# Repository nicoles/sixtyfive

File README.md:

# sixtyfive
 
A 65% keyboard. Using https://github.com/AcheronProject/Tsuki as a guide, wish me luck?

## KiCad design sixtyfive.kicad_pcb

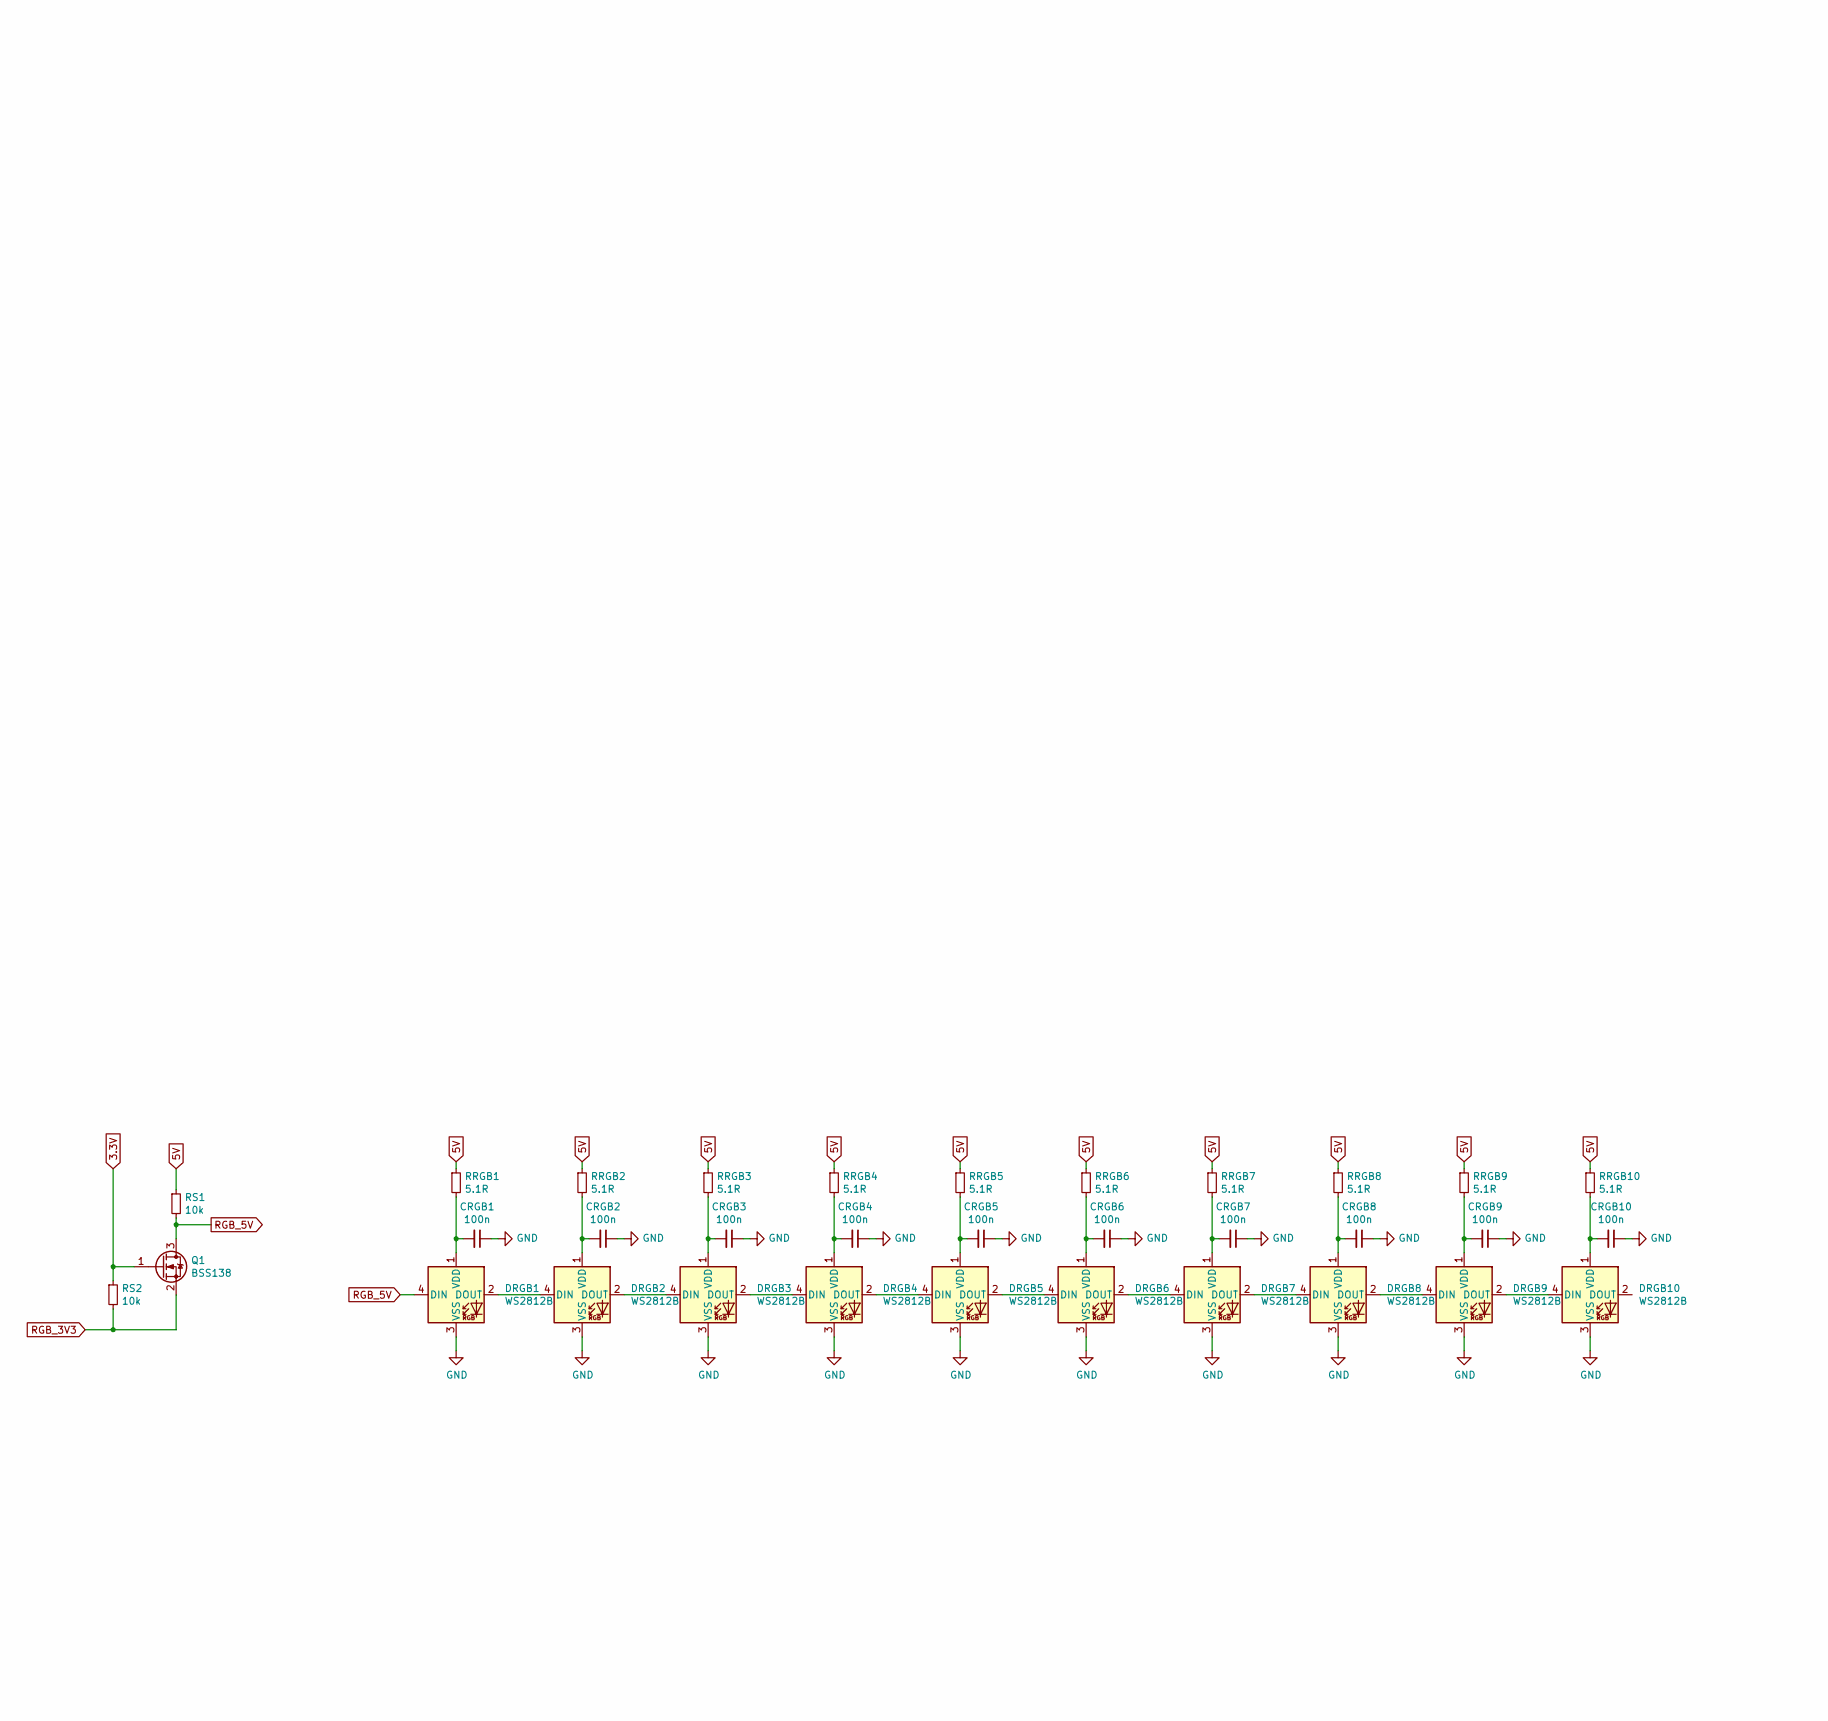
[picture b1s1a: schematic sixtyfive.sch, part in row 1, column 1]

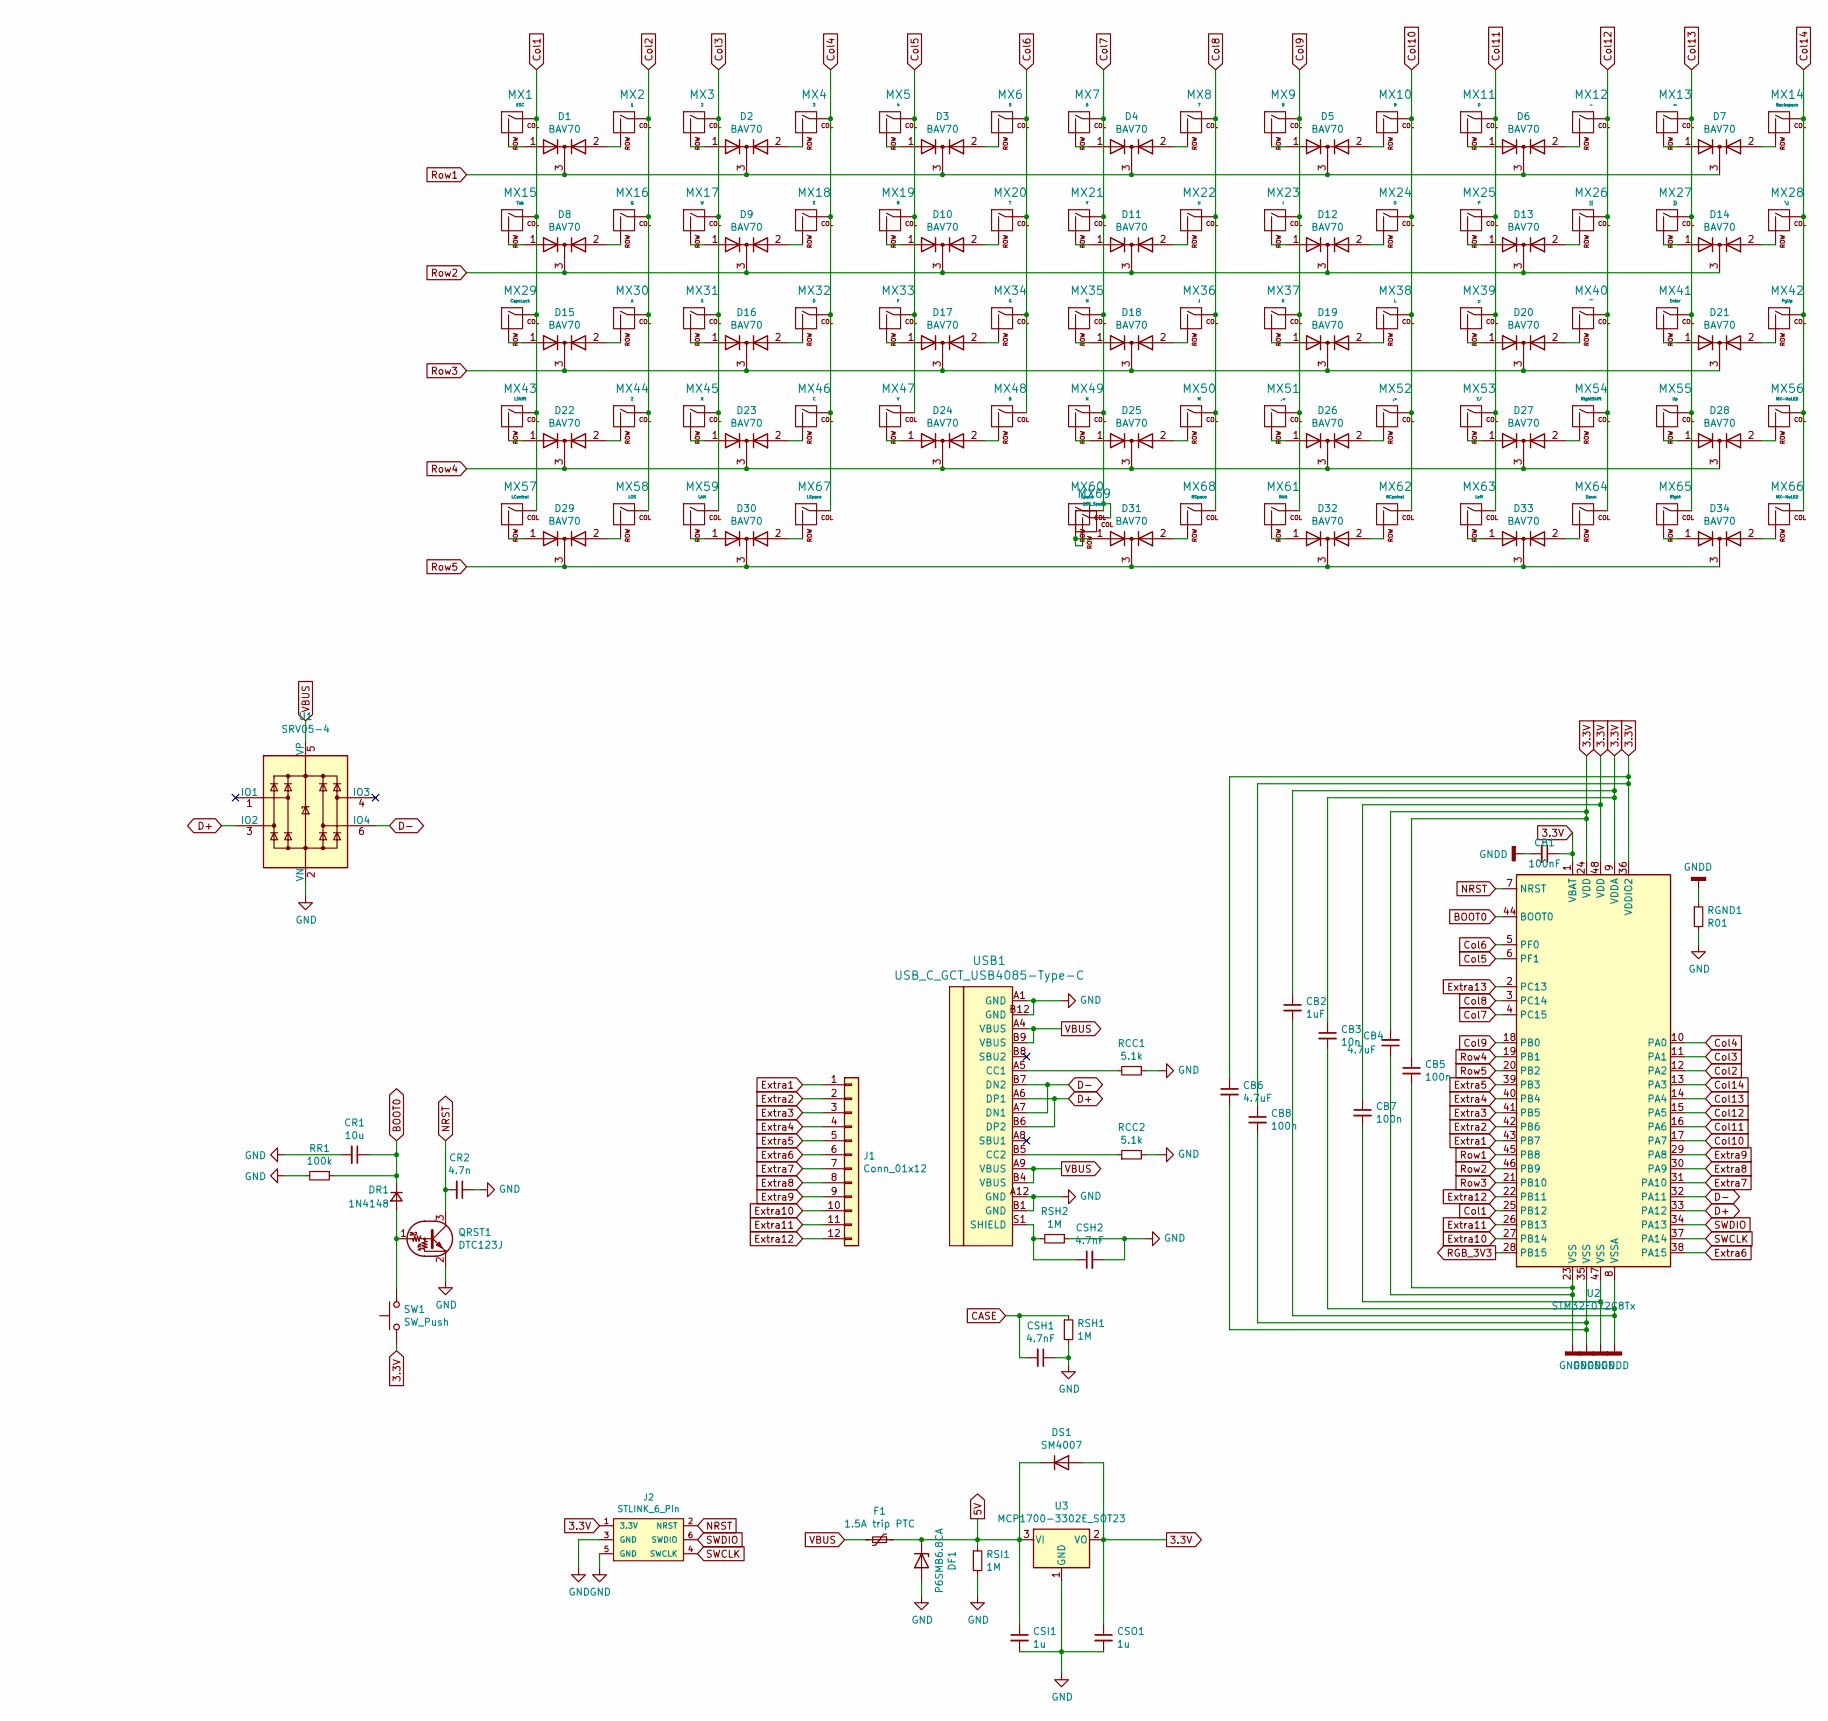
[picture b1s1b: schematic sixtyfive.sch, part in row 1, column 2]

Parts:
CB1: 100nF; C_0402_1005Metric; JLCCode C1525
CB2: 1uF; C_0402_1005Metric; JLCCode C52923
CB3: 10n; C_0402_1005Metric; JLCCode C15195
CB4, CB6: 4.7uF; C_0402_1005Metric; JLCCode C23733
CB5, CB7, CB8: 100n; C_0402_1005Metric; JLCCode C1525
CR1: 10u; C_0805_2012Metric; JLCCode C15850
CR2: 4.7n; C_0805_2012Metric; JLCCode C1744
CRGB1, CRGB2, CRGB3, CRGB4, CRGB5, CRGB6, CRGB7, CRGB8, CRGB9, CRGB10: 100n; C_0805_2012Metric
CSH1, CSH2: 4.7nF; C_0805_2012Metric; JLCCode C1744
CSI1: 1u; C_0805_2012Metric; JLCCode C28323
CSO1: 1u; C_0805_2012Metric; JLCCode C28323
D1, D2, D3, D4, D5, D6, D7, D8, D9, D10, D11, D12, D13, D14, D15, D16, D17, D18, D19, D20, D21, D22, D23, D24, D25, D26, D27, D28, D29, D30, D31, D32, D33, D34: BAV70; SOT-23; JLCCode C68978
DF1: P6SMB6.8CA; D_SMB; JLCCode C78395
DR1: 1N4148; D_SOD-123; JLCCode C81598
DRGB1, DRGB2, DRGB3, DRGB4, DRGB5, DRGB6, DRGB7, DRGB8, DRGB9, DRGB10: WS2812B; LED_WS2812B_PLCC4_5.0x5.0mm_P3.2mm; JLCCode C114586
DS1: SM4007; D_SOD-123F; JLCCode C64898
F1: 1.5A trip PTC; Fuse_1812_4532Metric; JLCCode C84140
J1: Conn_01x12; PinHeader_1x12_P2.54mm_Vertical
J2: STLINK_6_Pin; 2X3_LOCK
MX1: ESC; MXOnly-1U-Hotswap
MX2: 1; MXOnly-1U-Hotswap
MX3: 2; MXOnly-1U-Hotswap
MX4: 3; MXOnly-1U-Hotswap
MX5: 4; MXOnly-1U-Hotswap
MX6: 5; MXOnly-1U-Hotswap
MX7: 6; MXOnly-1U-Hotswap
MX8: 7; MXOnly-1U-Hotswap
MX9: 8; MXOnly-1U-Hotswap
MX10: 9; MXOnly-1U-Hotswap
MX11: 0; MXOnly-1U-Hotswap
MX12: -; MXOnly-1U-Hotswap
MX13: =; MXOnly-1U-Hotswap
MX14: Backspace; MXOnly-2U-Hotswap
MX15: Tab; MXOnly-1.5U-Hotswap
MX16: Q; MXOnly-1U-Hotswap
MX17: W; MXOnly-1U-Hotswap
MX18: E; MXOnly-1U-Hotswap
MX19: R; MXOnly-1U-Hotswap
MX20: T; MXOnly-1U-Hotswap
MX21: Y; MXOnly-1U-Hotswap
MX22: U; MXOnly-1U-Hotswap
MX23: I; MXOnly-1U-Hotswap
MX24: O; MXOnly-1U-Hotswap
MX25: P; MXOnly-1U-Hotswap
MX26: [{; MXOnly-1U-Hotswap
MX27: ]}; MXOnly-1U-Hotswap
MX28: \\|; MXOnly-1.5U-Hotswap
MX29: CapsLock; MXOnly-1.75U-Hotswap
MX30: A; MXOnly-1U-Hotswap
MX31: S; MXOnly-1U-Hotswap
MX32: D; MXOnly-1U-Hotswap
MX33: F; MXOnly-1U-Hotswap
MX34: G; MXOnly-1U-Hotswap
MX35: H; MXOnly-1U-Hotswap
MX36: J; MXOnly-1U-Hotswap
MX37: K; MXOnly-1U-Hotswap
MX38: L; MXOnly-1U-Hotswap
MX39: :;; MXOnly-1U-Hotswap
MX40: \"'; MXOnly-1U-Hotswap
MX41: Enter; MXOnly-2.25U-Hotswap
MX42: PgUp; MXOnly-1U-Hotswap
MX43: LShift; MXOnly-2.25U-Hotswap
MX44: Z; MXOnly-1U-Hotswap
MX45: X; MXOnly-1U-Hotswap
MX46: C; MXOnly-1U-Hotswap
MX47: V; MXOnly-1U-Hotswap
MX48: B; MXOnly-1U-Hotswap
MX49: N; MXOnly-1U-Hotswap
MX50: M; MXOnly-1U-Hotswap
MX51: ,<; MXOnly-1U-Hotswap
MX52: .>; MXOnly-1U-Hotswap
MX53: ?/; MXOnly-1U-Hotswap
MX54: RightShift; MXOnly-1.75U-Hotswap
MX55: Up; MXOnly-1U-Hotswap
MX56, MX66: MX-NoLED; MXOnly-1U-Hotswap
MX57: LControl; MXOnly-1.25U-Hotswap
MX58: LOS; MXOnly-1.25U-Hotswap
MX59: LAlt; MXOnly-1.25U-Hotswap
MX60: Space; MXOnly-6.25U-Hotswap-ReversedStabilizers
MX61: RAlt; MXOnly-1.25U-Hotswap
MX62: RControl; MXOnly-1.25U-Hotswap
MX63: Left; MXOnly-1U-Hotswap
MX64: Down; MXOnly-1U-Hotswap
MX65: Right; MXOnly-1U-Hotswap
MX67: LSpace; MXOnly-2.75U-Hotswap
MX68: RSpace; MXOnly-2.25U-Hotswap
MX69: 125_Space; MXOnly-1.25U-Hotswap
Q1: BSS138; SOT-23; JLCCode C193019
QRST1: DTC123J; SOT-23; JLCCode C111724
RCC1, RCC2: 5.1k; R_0805_2012Metric; JLCCode C27834
RGND1: R01; R_1206_3216Metric; JLCCode C127703
RR1: 100k; R_1206_3216Metric; JLCCode C17900
RRGB1, RRGB2, RRGB3, RRGB4, RRGB5, RRGB6, RRGB7, RRGB8, RRGB9, RRGB10: 5.1R; R_0805_2012Metric; JLCCode C17724
RS1, RS2: 10k; R_1206_3216Metric; JLCCode C17902
RSH1, RSH2: 1M; R_0805_2012Metric; JLCCode C17514
RSI1: 1M; R_0805_2012Metric; JLCCode C17514
SW1: SW_Push; smdPushBtn; JLCCode C318884
U1: SRV05-4; SOT-23-6; JLCCode C85364
U2: STM32F072C8Tx; LQFP-48_7x7mm_P0.5mm; JLCCode C80488
U3: MCP1700-3302E_SOT23; SOT-23; JLCCode C39051
USB1: USB_C_GCT_USB4085-Type-C; USB_C_Receptacle_GCT_USB4085

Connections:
5V: CSI1.1, DF1.1 (K), DS1.1 (K), F1.1, RRGB1.1, RRGB2.1, RRGB3.1, RRGB4.1, RRGB5.1, RRGB6.1, RRGB7.1, RRGB8.1, RRGB9.1, RRGB10.1, RS1.1, RSI1.1, U3.3 (VI)
+3V3: CB1.1, CB2.1, CB3.1, CB4.2, CB5.1, CB6.1, CB7.1, CB8.1, CSO1.1, DS1.2 (A), J2.1 (3.3V), Q1.1 (G), RS2.1, SW1.1, U2.1 (VBAT), U2.9 (VDDA), U2.24 (VDD), U2.36 (VDDIO2), U2.48 (VDD), U3.2 (VO)
BOOT0: CR1.1, DR1.1 (K), RR1.1, U2.44 (BOOT0)
CASE: CSH1.2, RSH1.1
Col1: MX1.1 (COL), MX15.1 (COL), MX29.1 (COL), MX43.1 (COL), MX57.1 (COL), U2.25 (PB12)
Col2: MX2.1 (COL), MX16.1 (COL), MX30.1 (COL), MX44.1 (COL), MX58.1 (COL), U2.12 (PA2)
Col3: MX3.1 (COL), MX17.1 (COL), MX31.1 (COL), MX45.1 (COL), MX59.1 (COL), U2.11 (PA1)
Col4: MX4.1 (COL), MX18.1 (COL), MX32.1 (COL), MX46.1 (COL), MX67.1 (COL), U2.10 (PA0)
Col5: MX5.1 (COL), MX19.1 (COL), MX33.1 (COL), MX47.1 (COL), U2.6 (PF1)
Col6: MX6.1 (COL), MX20.1 (COL), MX34.1 (COL), MX48.1 (COL), U2.5 (PF0)
Col7: MX7.1 (COL), MX21.1 (COL), MX35.1 (COL), MX49.1 (COL), MX60.1 (COL), MX69.1 (COL), U2.4 (PC15)
Col8: MX8.1 (COL), MX22.1 (COL), MX36.1 (COL), MX50.1 (COL), MX68.1 (COL), U2.3 (PC14)
Col9: MX9.1 (COL), MX23.1 (COL), MX37.1 (COL), MX51.1 (COL), MX61.1 (COL), U2.18 (PB0)
Col10: MX10.1 (COL), MX24.1 (COL), MX38.1 (COL), MX52.1 (COL), MX62.1 (COL), U2.17 (PA7)
Col11: MX11.1 (COL), MX25.1 (COL), MX39.1 (COL), MX53.1 (COL), MX63.1 (COL), U2.16 (PA6)
Col12: MX12.1 (COL), MX26.1 (COL), MX40.1 (COL), MX54.1 (COL), MX64.1 (COL), U2.15 (PA5)
Col13: MX13.1 (COL), MX27.1 (COL), MX41.1 (COL), MX55.1 (COL), MX65.1 (COL), U2.14 (PA4)
Col14: MX14.1 (COL), MX28.1 (COL), MX42.1 (COL), MX56.1 (COL), MX66.1 (COL), U2.13 (PA3)
D+: U1.3 (IO2), U2.33 (PA12), USB1.A6 (DP1), USB1.B6 (DP2)
D-: U1.6 (IO4), U2.32 (PA11), USB1.A7 (DN1), USB1.B7 (DN2)
Extra1: J1.1, U2.43 (PB7)
Extra2: J1.2, U2.42 (PB6)
Extra3: J1.3, U2.41 (PB5)
Extra4: J1.4, U2.40 (PB4)
Extra5: J1.5, U2.39 (PB3)
Extra6: J1.6, U2.38 (PA15)
Extra7: J1.7, U2.31 (PA10)
Extra8: J1.8, U2.30 (PA9)
Extra9: J1.9, U2.29 (PA8)
Extra10: J1.10, U2.27 (PB14)
Extra11: J1.11, U2.26 (PB13)
Extra12: J1.12, U2.22 (PB11)
GND: CR1.2, CR2.1, CRGB1.1, CRGB2.1, CRGB3.1, CRGB4.1, CRGB5.1, CRGB6.1, CRGB7.1, CRGB8.1, CRGB9.1, CRGB10.1, CSH1.1, CSH2.2, CSI1.2, CSO1.2, DF1.2 (A), DRGB1.3 (VSS), DRGB2.3 (VSS), DRGB3.3 (VSS), DRGB4.3 (VSS), DRGB5.3 (VSS), DRGB6.3 (VSS), DRGB7.3 (VSS), DRGB8.3 (VSS), DRGB9.3 (VSS), DRGB10.3 (VSS), J2.3 (GND), J2.5 (GND), QRST1.2 (E), RCC1.1, RCC2.2, RGND1.2, RR1.2, RSH1.2, RSH2.1, RSI1.2, U1.2 (VN), U3.1 (GND), USB1.A1 (GND), USB1.A12 (GND), USB1.B1 (GND), USB1.B12 (GND)
GNDD: CB1.2, CB2.2, CB3.2, CB4.1, CB5.2, CB6.2, CB7.2, CB8.2, RGND1.1, U2.8 (VSSA), U2.23 (VSS), U2.35 (VSS), U2.47 (VSS)
NRST: CR2.2, J2.2 (NRST), QRST1.3 (C), U2.7 (NRST)
unnamed: CRGB1.2, DRGB1.1 (VDD), RRGB1.2
unnamed: CRGB2.2, DRGB2.1 (VDD), RRGB2.2
unnamed: CRGB3.2, DRGB3.1 (VDD), RRGB3.2
unnamed: CRGB4.2, DRGB4.1 (VDD), RRGB4.2
unnamed: CRGB5.2, DRGB5.1 (VDD), RRGB5.2
unnamed: CRGB6.2, DRGB6.1 (VDD), RRGB6.2
unnamed: CRGB7.2, DRGB7.1 (VDD), RRGB7.2
unnamed: CRGB8.2, DRGB8.1 (VDD), RRGB8.2
unnamed: CRGB9.2, DRGB9.1 (VDD), RRGB9.2
unnamed: CRGB10.2, DRGB10.1 (VDD), RRGB10.2
unnamed: CSH2.1, RSH2.2, USB1.S1 (SHIELD)
unnamed: D1.1 (A), MX1.2 (ROW)
unnamed: D1.2 (A), MX2.2 (ROW)
unnamed: D2.1 (A), MX3.2 (ROW)
unnamed: D2.2 (A), MX4.2 (ROW)
unnamed: D3.1 (A), MX5.2 (ROW)
unnamed: D3.2 (A), MX6.2 (ROW)
unnamed: D4.1 (A), MX7.2 (ROW)
unnamed: D4.2 (A), MX8.2 (ROW)
unnamed: D5.1 (A), MX9.2 (ROW)
unnamed: D5.2 (A), MX10.2 (ROW)
unnamed: D6.1 (A), MX11.2 (ROW)
unnamed: D6.2 (A), MX12.2 (ROW)
unnamed: D7.1 (A), MX13.2 (ROW)
unnamed: D7.2 (A), MX14.2 (ROW)
unnamed: D8.1 (A), MX15.2 (ROW)
unnamed: D8.2 (A), MX16.2 (ROW)
unnamed: D9.1 (A), MX17.2 (ROW)
unnamed: D9.2 (A), MX18.2 (ROW)
unnamed: D10.1 (A), MX19.2 (ROW)
unnamed: D10.2 (A), MX20.2 (ROW)
unnamed: D11.1 (A), MX21.2 (ROW)
unnamed: D11.2 (A), MX22.2 (ROW)
unnamed: D12.1 (A), MX23.2 (ROW)
unnamed: D12.2 (A), MX24.2 (ROW)
unnamed: D13.1 (A), MX25.2 (ROW)
unnamed: D13.2 (A), MX26.2 (ROW)
unnamed: D14.1 (A), MX27.2 (ROW)
unnamed: D14.2 (A), MX28.2 (ROW)
unnamed: D15.1 (A), MX29.2 (ROW)
unnamed: D15.2 (A), MX30.2 (ROW)
unnamed: D16.1 (A), MX31.2 (ROW)
unnamed: D16.2 (A), MX32.2 (ROW)
unnamed: D17.1 (A), MX33.2 (ROW)
unnamed: D17.2 (A), MX34.2 (ROW)
unnamed: D18.1 (A), MX35.2 (ROW)
unnamed: D18.2 (A), MX36.2 (ROW)
unnamed: D19.1 (A), MX37.2 (ROW)
unnamed: D19.2 (A), MX38.2 (ROW)
unnamed: D20.1 (A), MX39.2 (ROW)
unnamed: D20.2 (A), MX40.2 (ROW)
unnamed: D21.1 (A), MX41.2 (ROW)
unnamed: D21.2 (A), MX42.2 (ROW)
unnamed: D22.1 (A), MX43.2 (ROW)
unnamed: D22.2 (A), MX44.2 (ROW)
unnamed: D23.1 (A), MX45.2 (ROW)
unnamed: D23.2 (A), MX46.2 (ROW)
unnamed: D24.1 (A), MX47.2 (ROW)
unnamed: D24.2 (A), MX48.2 (ROW)
unnamed: D25.1 (A), MX49.2 (ROW)
unnamed: D25.2 (A), MX50.2 (ROW)
unnamed: D26.1 (A), MX51.2 (ROW)
unnamed: D26.2 (A), MX52.2 (ROW)
unnamed: D27.1 (A), MX53.2 (ROW)
unnamed: D27.2 (A), MX54.2 (ROW)
unnamed: D28.1 (A), MX55.2 (ROW)
unnamed: D28.2 (A), MX56.2 (ROW)
unnamed: D29.1 (A), MX57.2 (ROW)
unnamed: D29.2 (A), MX58.2 (ROW)
unnamed: D30.1 (A), MX59.2 (ROW)
unnamed: D30.2 (A), MX67.2 (ROW)
unnamed: D31.1 (A), MX60.2 (ROW), MX69.2 (ROW)
unnamed: D31.2 (A), MX68.2 (ROW)
unnamed: D32.1 (A), MX61.2 (ROW)
unnamed: D32.2 (A), MX62.2 (ROW)
unnamed: D33.1 (A), MX63.2 (ROW)
unnamed: D33.2 (A), MX64.2 (ROW)
unnamed: D34.1 (A), MX65.2 (ROW)
unnamed: D34.2 (A), MX66.2 (ROW)
unnamed: DR1.2 (A), QRST1.1 (B), SW1.2
unnamed: DRGB1.2 (DOUT), DRGB2.4 (DIN)
unnamed: DRGB2.2 (DOUT), DRGB3.4 (DIN)
unnamed: DRGB3.2 (DOUT), DRGB4.4 (DIN)
unnamed: DRGB4.2 (DOUT), DRGB5.4 (DIN)
unnamed: DRGB5.2 (DOUT), DRGB6.4 (DIN)
unnamed: DRGB6.2 (DOUT), DRGB7.4 (DIN)
unnamed: DRGB7.2 (DOUT), DRGB8.4 (DIN)
unnamed: DRGB8.2 (DOUT), DRGB9.4 (DIN)
unnamed: DRGB9.2 (DOUT), DRGB10.4 (DIN)
unnamed: RCC1.2, USB1.A5 (CC1)
unnamed: RCC2.1, USB1.B5 (CC2)
RGB_3V3: Q1.2 (S), RS2.2, U2.28 (PB15)
RGB_5V: DRGB1.4 (DIN), Q1.3 (D), RS1.2
Row1: D1.3 (K), D2.3 (K), D3.3 (K), D4.3 (K), D5.3 (K), D6.3 (K), D7.3 (K), U2.45 (PB8)
Row2: D8.3 (K), D9.3 (K), D10.3 (K), D11.3 (K), D12.3 (K), D13.3 (K), D14.3 (K), U2.46 (PB9)
Row3: D15.3 (K), D16.3 (K), D17.3 (K), D18.3 (K), D19.3 (K), D20.3 (K), D21.3 (K), U2.21 (PB10)
Row4: D22.3 (K), D23.3 (K), D24.3 (K), D25.3 (K), D26.3 (K), D27.3 (K), D28.3 (K), U2.19 (PB1)
Row5: D29.3 (K), D30.3 (K), D31.3 (K), D32.3 (K), D33.3 (K), D34.3 (K), U2.20 (PB2)
SWCLK: J2.4 (SWCLK), U2.37 (PA14)
SWDIO: J2.6 (SWDIO), U2.34 (PA13)
VBUS: F1.2, U1.5 (VP), USB1.A4 (VBUS), USB1.A9 (VBUS), USB1.B4 (VBUS), USB1.B9 (VBUS)

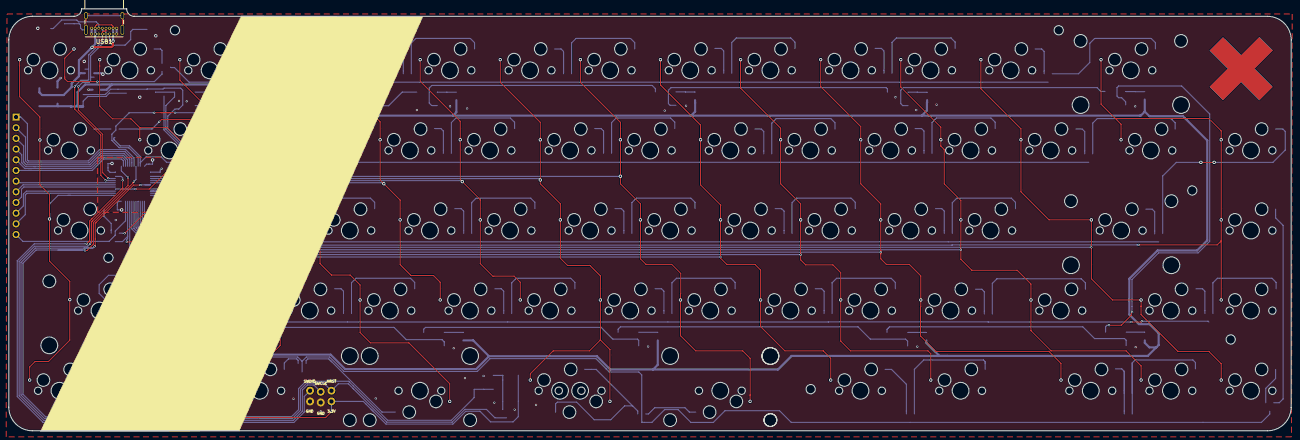
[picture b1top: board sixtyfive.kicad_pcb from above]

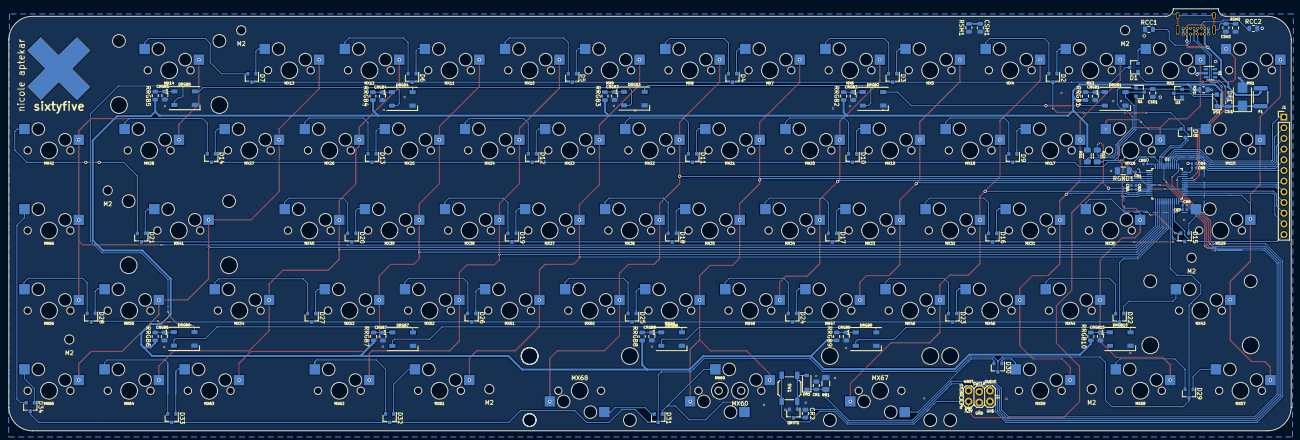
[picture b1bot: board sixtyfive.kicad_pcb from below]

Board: 2 copper layers, 305.0 x 100.3 mm, 176 parts (106 on the bottom side), 136 nets.

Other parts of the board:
M2, M2#2, M2#3, M2#4, M2#5, M2#6, M2#7: MountingHole_2.2mm_M2

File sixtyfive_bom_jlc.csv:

"Comment","Designator","Footprint","LCSC Part #"
"100nF","CB1","C_0402_1005Metric","C1525"
"1uF","CB2","C_0402_1005Metric","C52923"
"10n","CB3","C_0402_1005Metric","C15195"
"4.7uF","CB4,CB6","C_0402_1005Metric","C23733"
"100n","CB5,CB7,CB8","C_0402_1005Metric","C1525"
"10u","CR1","C_0805_2012Metric","C15850"
"4.7n","CR2","C_0805_2012Metric","C1744"
"100n","CRGB5,CRGB6,CRGB7,CRGB8,CRGB1,CRGB2,CRGB3,CRGB4,CRGB9,CRGB10","C_0805_2012Metric","C49678"
"4.7nF","CSH2,CSH1","C_0805_2012Metric","C1744"
"1u","CSI1","C_0805_2012Metric","C28323"
"1u","CSO1","C_0805_2012Metric","C28323"
"BAV70","D1,D2,D3,D4,D5,D6,D7,D14,D21,D13,D20,D12,D19,D26,D27,D28,D34,D33,D32,D31,D25,D18,D11,D10,D17,D24,D30,D23,D16,D9,D8,D15,D22,D29","SOT-23","C68978"
"P6SMB6.8CA","DF1","D_SMB","C78395"
"1N4148","DR1","D_SOD-123","C81598"
"WS2812B","DRGB5,DRGB6,DRGB7,DRGB8,DRGB1,DRGB2,DRGB3,DRGB4,DRGB9,DRGB10","LED_WS2812B_PLCC4_5.0x5.0mm_P3.2mm","C114586"
"SM4007","DS1","D_SOD-123F","C64898"
"1.5A trip PTC","F1","Fuse_1812_4532Metric","C84140"
"BSS138","Q1","SOT-23","C193019"
"DTC123J","QRST1","SOT-23","C111724"
"5.1k","RCC1,RCC2","R_0805_2012Metric","C27834"
"R01","RGND1","R_1206_3216Metric","C127703"
"100k","RR1","R_1206_3216Metric","C17900"
"5.1R","RRGB5,RRGB6,RRGB7,RRGB8,RRGB1,RRGB2,RRGB3,RRGB4,RRGB9,RRGB10","R_0805_2012Metric","C17724"
"10k","RS2,RS1","R_1206_3216Metric","C17902"
"1M","RSH2,RSH1","R_0805_2012Metric","C17514"
"1M","RSI1","R_0805_2012Metric","C17514"
"SW_Push","SW1","smdPushBtn","C318884"
"SRV05-4","U1","SOT-23-6","C85364"
"STM32F072C8Tx","U2","LQFP-48_7x7mm_P0.5mm","C80488"
"MCP1700-3302E_SOT23","U3","SOT-23","C39051"

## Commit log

2020-06-05 empty kicad proj
2020-06-05 added keeb submodules
2020-06-05 added libraries to kicad proj
2020-06-05 Started on schematic, dealing with cap nightmare
2020-06-06 diagrammed mcu
2020-06-06 Added rest of stuff I'm pulling in from Tsuki
2020-06-06 labeled everything? maybe?
2020-06-06 Added footprints for most things
2020-06-06 the smallest readme
2020-06-07 Placed all the switches, all the diodes!
2020-06-10 Placed rgb leds
2020-06-12 Pretty sure I wired up the whole matrix
2020-06-12 Matrix rewired to allow for 5v line for rgb, which is also wired up
2020-06-12 extras wired up, fills started around mcu
2020-06-12 added reset and jtag footprint
2020-06-12 Placed... everything? wired everything?
2020-06-13 Switched some components to "basic" parts, hopefully we good
2020-06-13 Adding gerbers, bom, cpl
2020-06-14 Redoing literally all the routing, switched diodes to common anode
2020-06-16 Rerouted everything, feels cleaner now?
2020-06-17 More routing changes, pulled things away from the edge and added more ground plane vias
2020-06-17 swapped a couple components for basic parts, rerouted
2020-06-17 Didn't quite save everything that last time.
    Just following the last bit of advice from the discord, swapping a couple components and rerouting some things
2020-06-17 Further discord feedback, using the srv05 properly now
    using the component right this time
2020-06-18 Added some decoration, changed the connector and rerouted a tiny bit
2020-06-18 Moved one diode
2020-06-24 As ordered v1
2020-06-24 Reorganized Schematic to be easier to read
2020-06-24 Further clarified schematic
